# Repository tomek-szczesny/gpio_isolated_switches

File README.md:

# gpio_isolated_switches
A GPIO header module with isolated switches, duh ;)

More details here:
https://forum.odroid.com/viewtopic.php?f=217&t=45637

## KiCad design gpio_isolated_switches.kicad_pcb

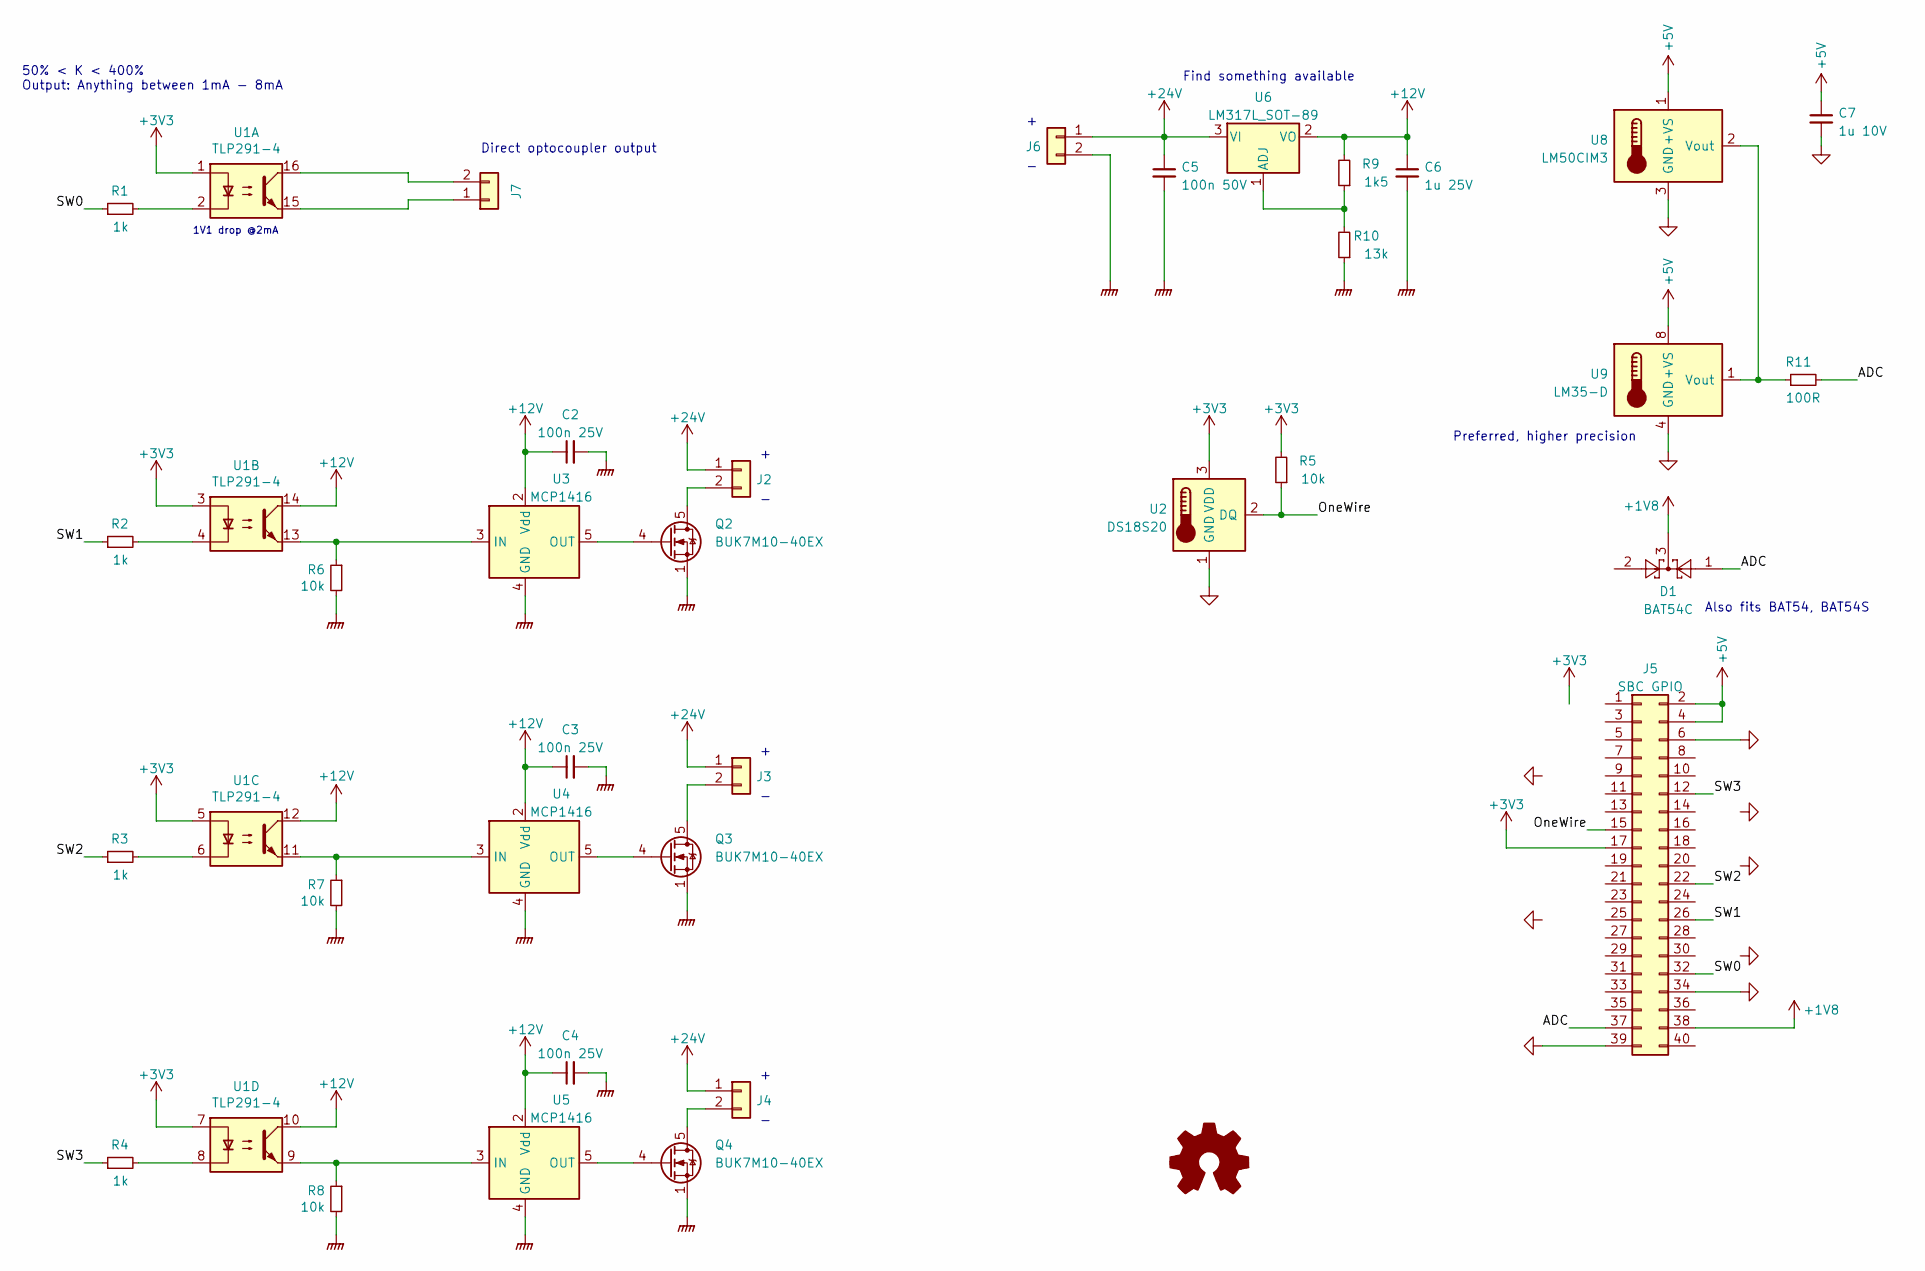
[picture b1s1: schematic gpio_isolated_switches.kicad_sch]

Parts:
C2, C3, C4: 100n 25V; C_0603_1608Metric
C5: 100n 50V; C_0603_1608Metric
C6: 1u 25V; C_0603_1608Metric
C7: 1u 10V; C_0603_1608Metric
D1: BAT54C; SOT-23
J2, J3, J4, J6: Conn_01x02; TerminalBlock_Altech_AK300-2_P5.00mm
J5: SBC GPIO; PinSocket_2x20_P2.54mm_Vertical
J7: Conn_01x02; PinHeader_1x02_P2.54mm_Horizontal
LOGO1: Logo_Open_Hardware_Small; OSHW-Logo2_9.8x8mm_SilkScreen
Q2, Q3, Q4: BUK7M10-40EX; LFPAK33
R1, R2, R3, R4: 1k; R_0603_1608Metric
R5, R6, R7, R8: 10k; R_0603_1608Metric
R9: 1k5; R_0603_1608Metric
R10: 13k; R_0603_1608Metric
R11: 100R; R_0603_1608Metric
U1: TLP291-4; SOIC-16_4.55x10.3mm_P1.27mm
U2: DS18S20; TO-92_Inline
U3, U4, U5: MCP1416; SOT-23-5
U6: LM317L_SOT-89; SOT-89-3
U8: LM50CIM3; SOT-23
U9: LM35-D; SOIC-8_3.9x4.9mm_P1.27mm

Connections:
+1V8: D1.3, J5.38
+3V3: J5.17, R5.2, U1.1, U1.3, U1.5, U1.7, U2.3 (VDD)
+5V: C7.1, J5.2, J5.4, U8.1 (+VS), U9.8 (+VS)
+12V: C2.1, C3.1, C4.1, C6.1, R9.2, U1.10, U1.12, U1.14, U3.2 (Vdd), U4.2 (Vdd), U5.2 (Vdd), U6.2 (VO)
+24V: C5.1, J2.1, J3.1, J4.1, J6.1, U6.3 (VI)
/ADC: D1.1, J5.37, R11.2
/OneWire: J5.15, R5.1, U2.2 (DQ)
/SW0: J5.32, R1.1
/SW1: J5.26, R2.1
/SW2: J5.22, R3.1
/SW3: J5.12, R4.1
GND: C7.2, J5.6, J5.34, J5.39, U2.1 (GND), U8.3 (GND), U9.4 (GND)
GNDPWR: C2.2, C3.2, C4.2, C5.2, C6.2, J6.2, Q2.1 (S), Q2.2 (S), Q2.3 (S), Q3.1 (S), Q3.2 (S), Q3.3 (S), Q4.1 (S), Q4.2 (S), Q4.3 (S), R6.2, R7.2, R8.2, R10.1, U3.4 (GND), U4.4 (GND), U5.4 (GND)
unnamed: J2.2, Q2.5 (D)
unnamed: J3.2, Q3.5 (D)
unnamed: J4.2, Q4.5 (D)
unnamed: J7.1, U1.15
unnamed: J7.2, U1.16
unnamed: Q2.4 (G), U3.5 (OUT)
unnamed: Q3.4 (G), U4.5 (OUT)
unnamed: Q4.4 (G), U5.5 (OUT)
unnamed: R1.2, U1.2
unnamed: R2.2, U1.4
unnamed: R3.2, U1.6
unnamed: R4.2, U1.8
unnamed: R6.1, U1.13, U3.3 (IN)
unnamed: R7.1, U1.11, U4.3 (IN)
unnamed: R8.1, U1.9, U5.3 (IN)
unnamed: R9.1, R10.2, U6.1 (ADJ)
unnamed: R11.1, U8.2 (Vout), U9.1 (Vout)

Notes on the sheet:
Direct optocoupler output
Also fits BAT54, BAT54S
Find something available
1V1 drop @2mA
Preferred, higher precision
50% < K < 400% Output: Anything between 1mA - 8mA

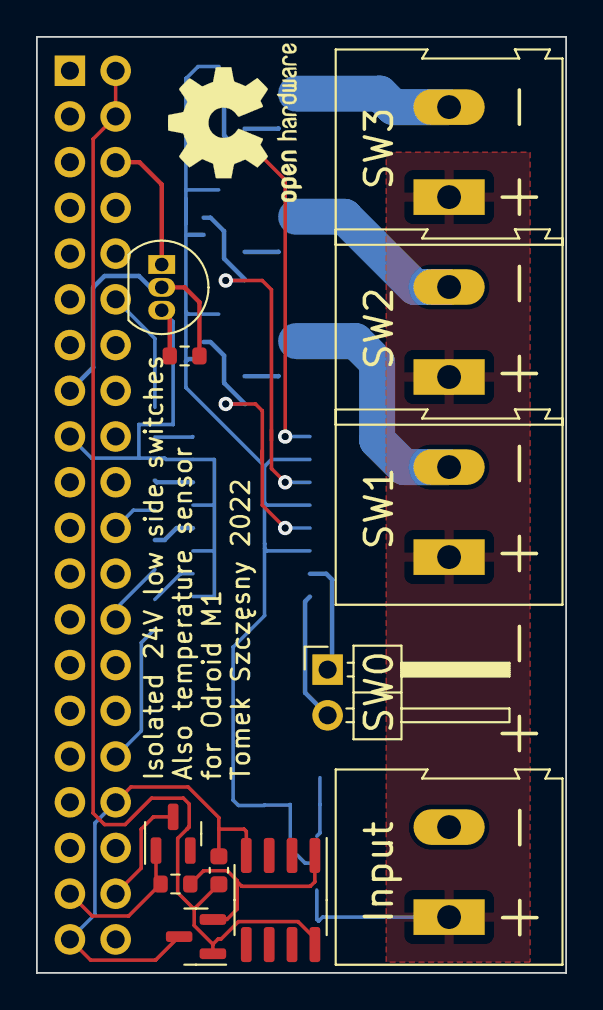
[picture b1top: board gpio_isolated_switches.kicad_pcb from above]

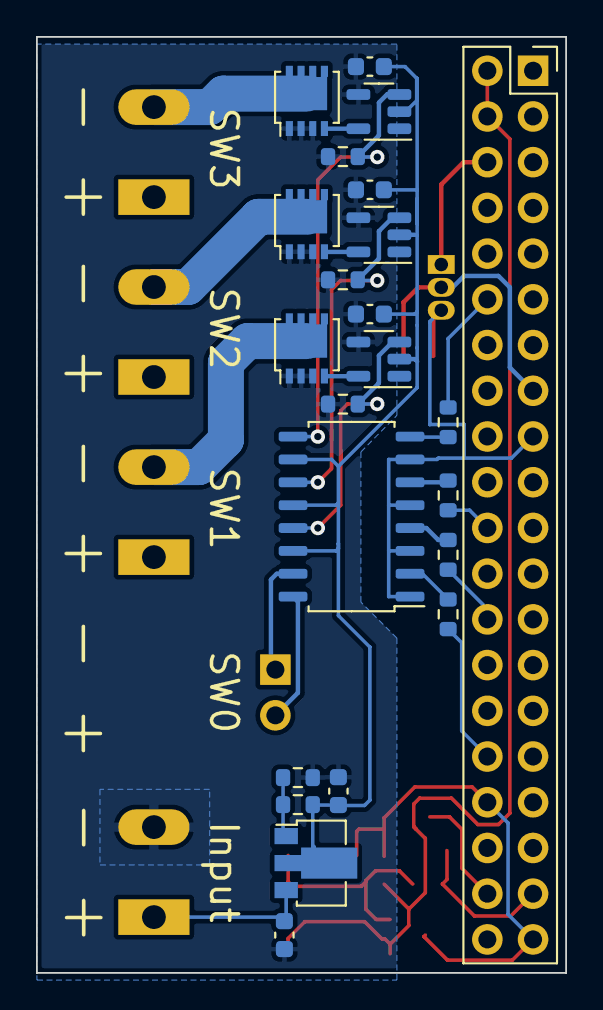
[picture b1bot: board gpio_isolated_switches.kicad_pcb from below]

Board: 2 copper layers, 29.4 x 52.0 mm, 36 parts (23 on the bottom side), 30 nets.

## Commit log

2022-11-09 Added link to relevant forum
2022-11-25 Adding SW0 direct output from optocoupler
2022-11-25 Adding production files
2022-11-25 Removed SW0 switch, left direct optocoupler output only
2022-11-27 Adding DS18B20 as an optional temperature sensor
